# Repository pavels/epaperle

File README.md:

See project page: [https://hackaday.io/project/29529-epaperle](https://hackaday.io/project/29529-epaperle)

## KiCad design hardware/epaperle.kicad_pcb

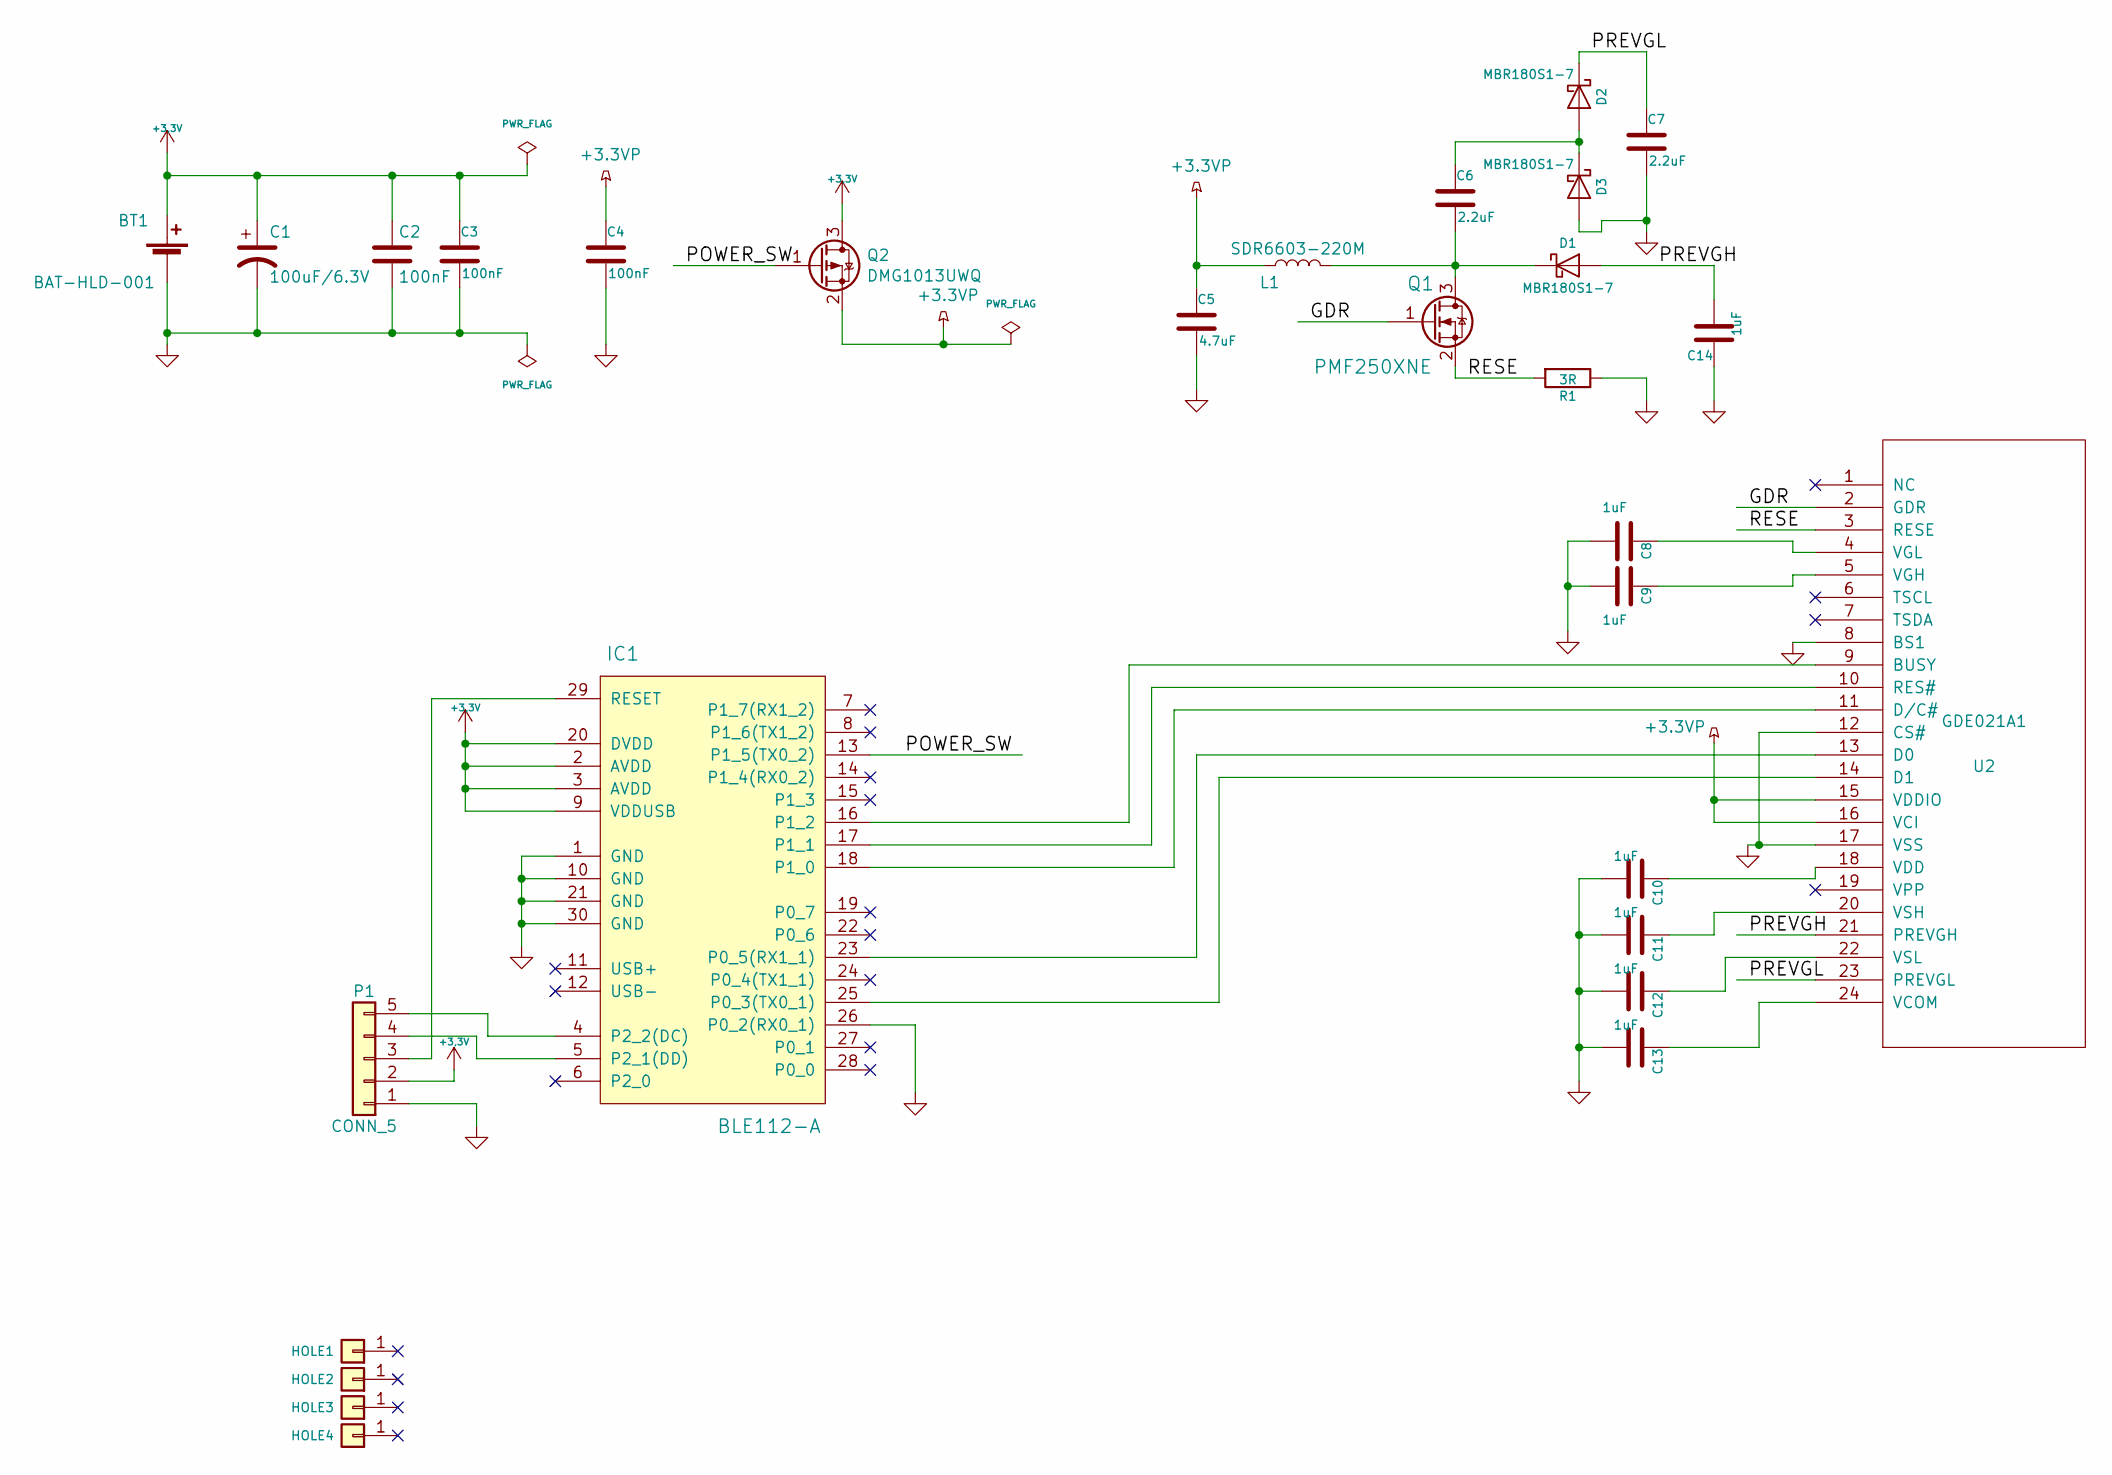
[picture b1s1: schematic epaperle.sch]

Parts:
BT1: BAT-HLD-001
C1: 100uF/6.3V; CP_Tantalum_Case-B_EIA-3528-21_Reflow
C2, C3, C4: 100nF; C_1206
C5: 4.7uF; C_1206
C6, C7: 2.2uF; C_1206
C8, C9, C10, C11, C12, C13, C14: 1uF; C_1206
D1, D2, D3: MBR180S1-7; D_SOD-123
HOLE1, HOLE2, HOLE3, HOLE4: HOLE; MountingHole_3.2mm_M3_Pad
IC1: BLE112-A
L1: SDR6603-220M; SDR6603
P1: CONN_5; PAD_1.5mm*2.5mm_5x100mil
Q1: PMF250XNE; SOT-323_SC-70
Q2: DMG1013UWQ; SOT-323_SC-70
R1: 3R; R_1206
U2: GDE021A1; Hirose_FH12A-24S-0.5SH

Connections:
+3.3VP: C4.1, C5.1, L1.1, Q2.2 (S), U2.15 (VDDIO), U2.16 (VCI)
+3V3: BT1.1 (+), C1.1, C2.1, C3.1, IC1.2 (AVDD), IC1.3 (AVDD), IC1.9 (VDDUSB), IC1.20 (DVDD), P1.2, Q2.3 (D)
/GDR: Q1.1 (G), U2.2 (GDR)
/POWER_SW: IC1.13 (P1_5(TX0_2)), Q2.1 (G)
/PREVGH: C14.2, D1.2 (A), U2.21 (PREVGH)
/PREVGL: C7.1, D2.1 (K), U2.23 (PREVGL)
/RESE: Q1.2 (S), R1.2, U2.3 (RESE)
GND: BT1.2 (-), C1.2, C2.2, C3.2, C4.2, C5.2, C7.2, C8.2, C9.2, C10.2, C11.2, C12.2, C13.2, C14.1, D3.2 (A), IC1.1 (GND), IC1.10 (GND), IC1.21 (GND), IC1.26 (P0_2(RX0_1)), IC1.30 (GND), P1.1, R1.1, U2.8 (BS1), U2.12 (CS#), U2.17 (VSS)
unnamed: C6.1, D2.2 (A), D3.1 (K)
unnamed: C6.2, D1.1 (K), L1.2, Q1.3 (D)
unnamed: C8.1, U2.4 (VGL)
unnamed: C9.1, U2.5 (VGH)
unnamed: C10.1, U2.18 (VDD)
unnamed: C11.1, U2.20 (VSH)
unnamed: C12.1, U2.22 (VSL)
unnamed: C13.1, U2.24 (VCOM)
unnamed: IC1.4 (P2_2(DC)), P1.5
unnamed: IC1.5 (P2_1(DD)), P1.4
unnamed: IC1.16 (P1_2), U2.9 (BUSY)
unnamed: IC1.17 (P1_1), U2.10 (RES#)
unnamed: IC1.18 (P1_0), U2.11 (D/C#)
unnamed: IC1.23 (P0_5(RX1_1)), U2.13 (D0)
unnamed: IC1.25 (P0_3(TX0_1)), U2.14 (D1)
unnamed: IC1.29 (RESET), P1.3

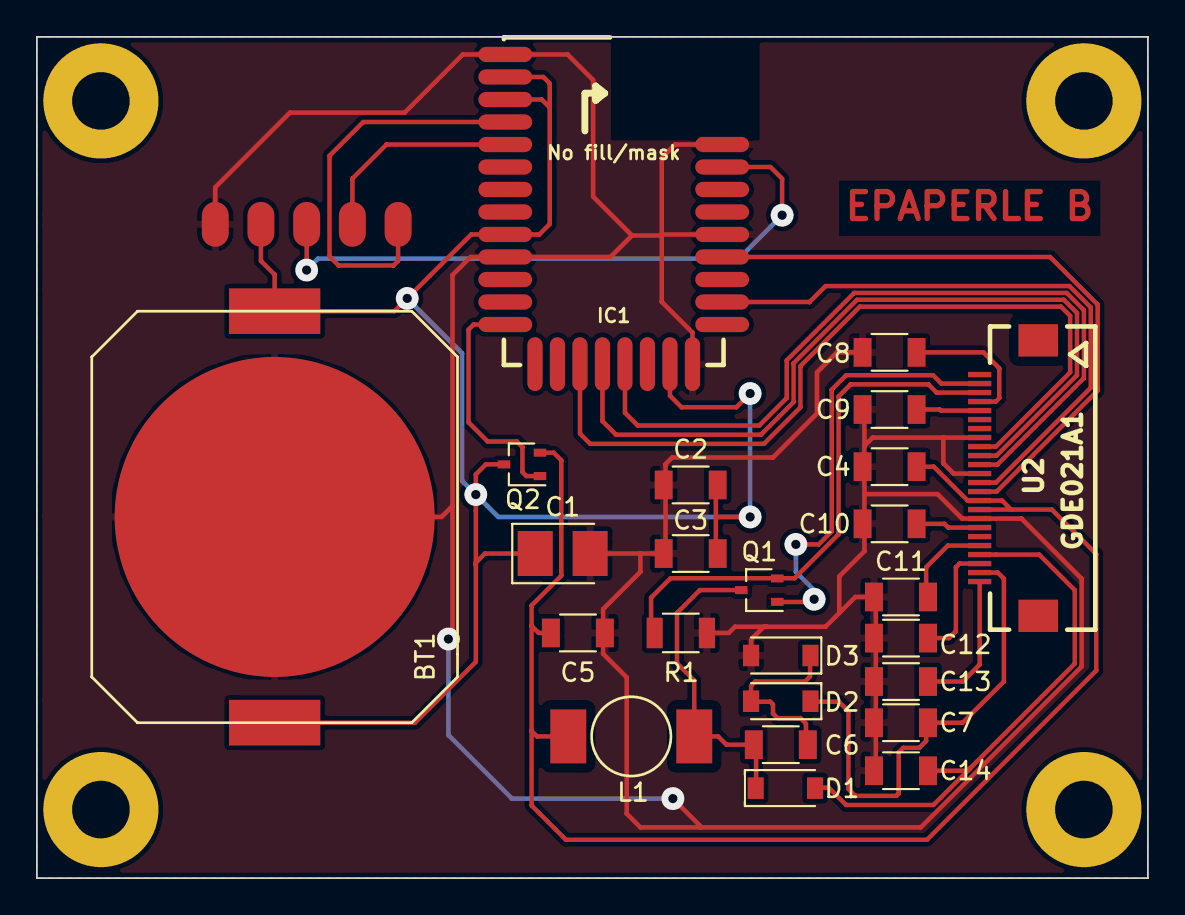
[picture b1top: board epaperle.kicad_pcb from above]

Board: 2 copper layers, 61.7 x 46.7 mm, 29 parts (0 on the bottom side), 24 nets.

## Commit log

2018-01-07 info docs
2018-01-07 schematics export
2018-01-08 bom fixes
